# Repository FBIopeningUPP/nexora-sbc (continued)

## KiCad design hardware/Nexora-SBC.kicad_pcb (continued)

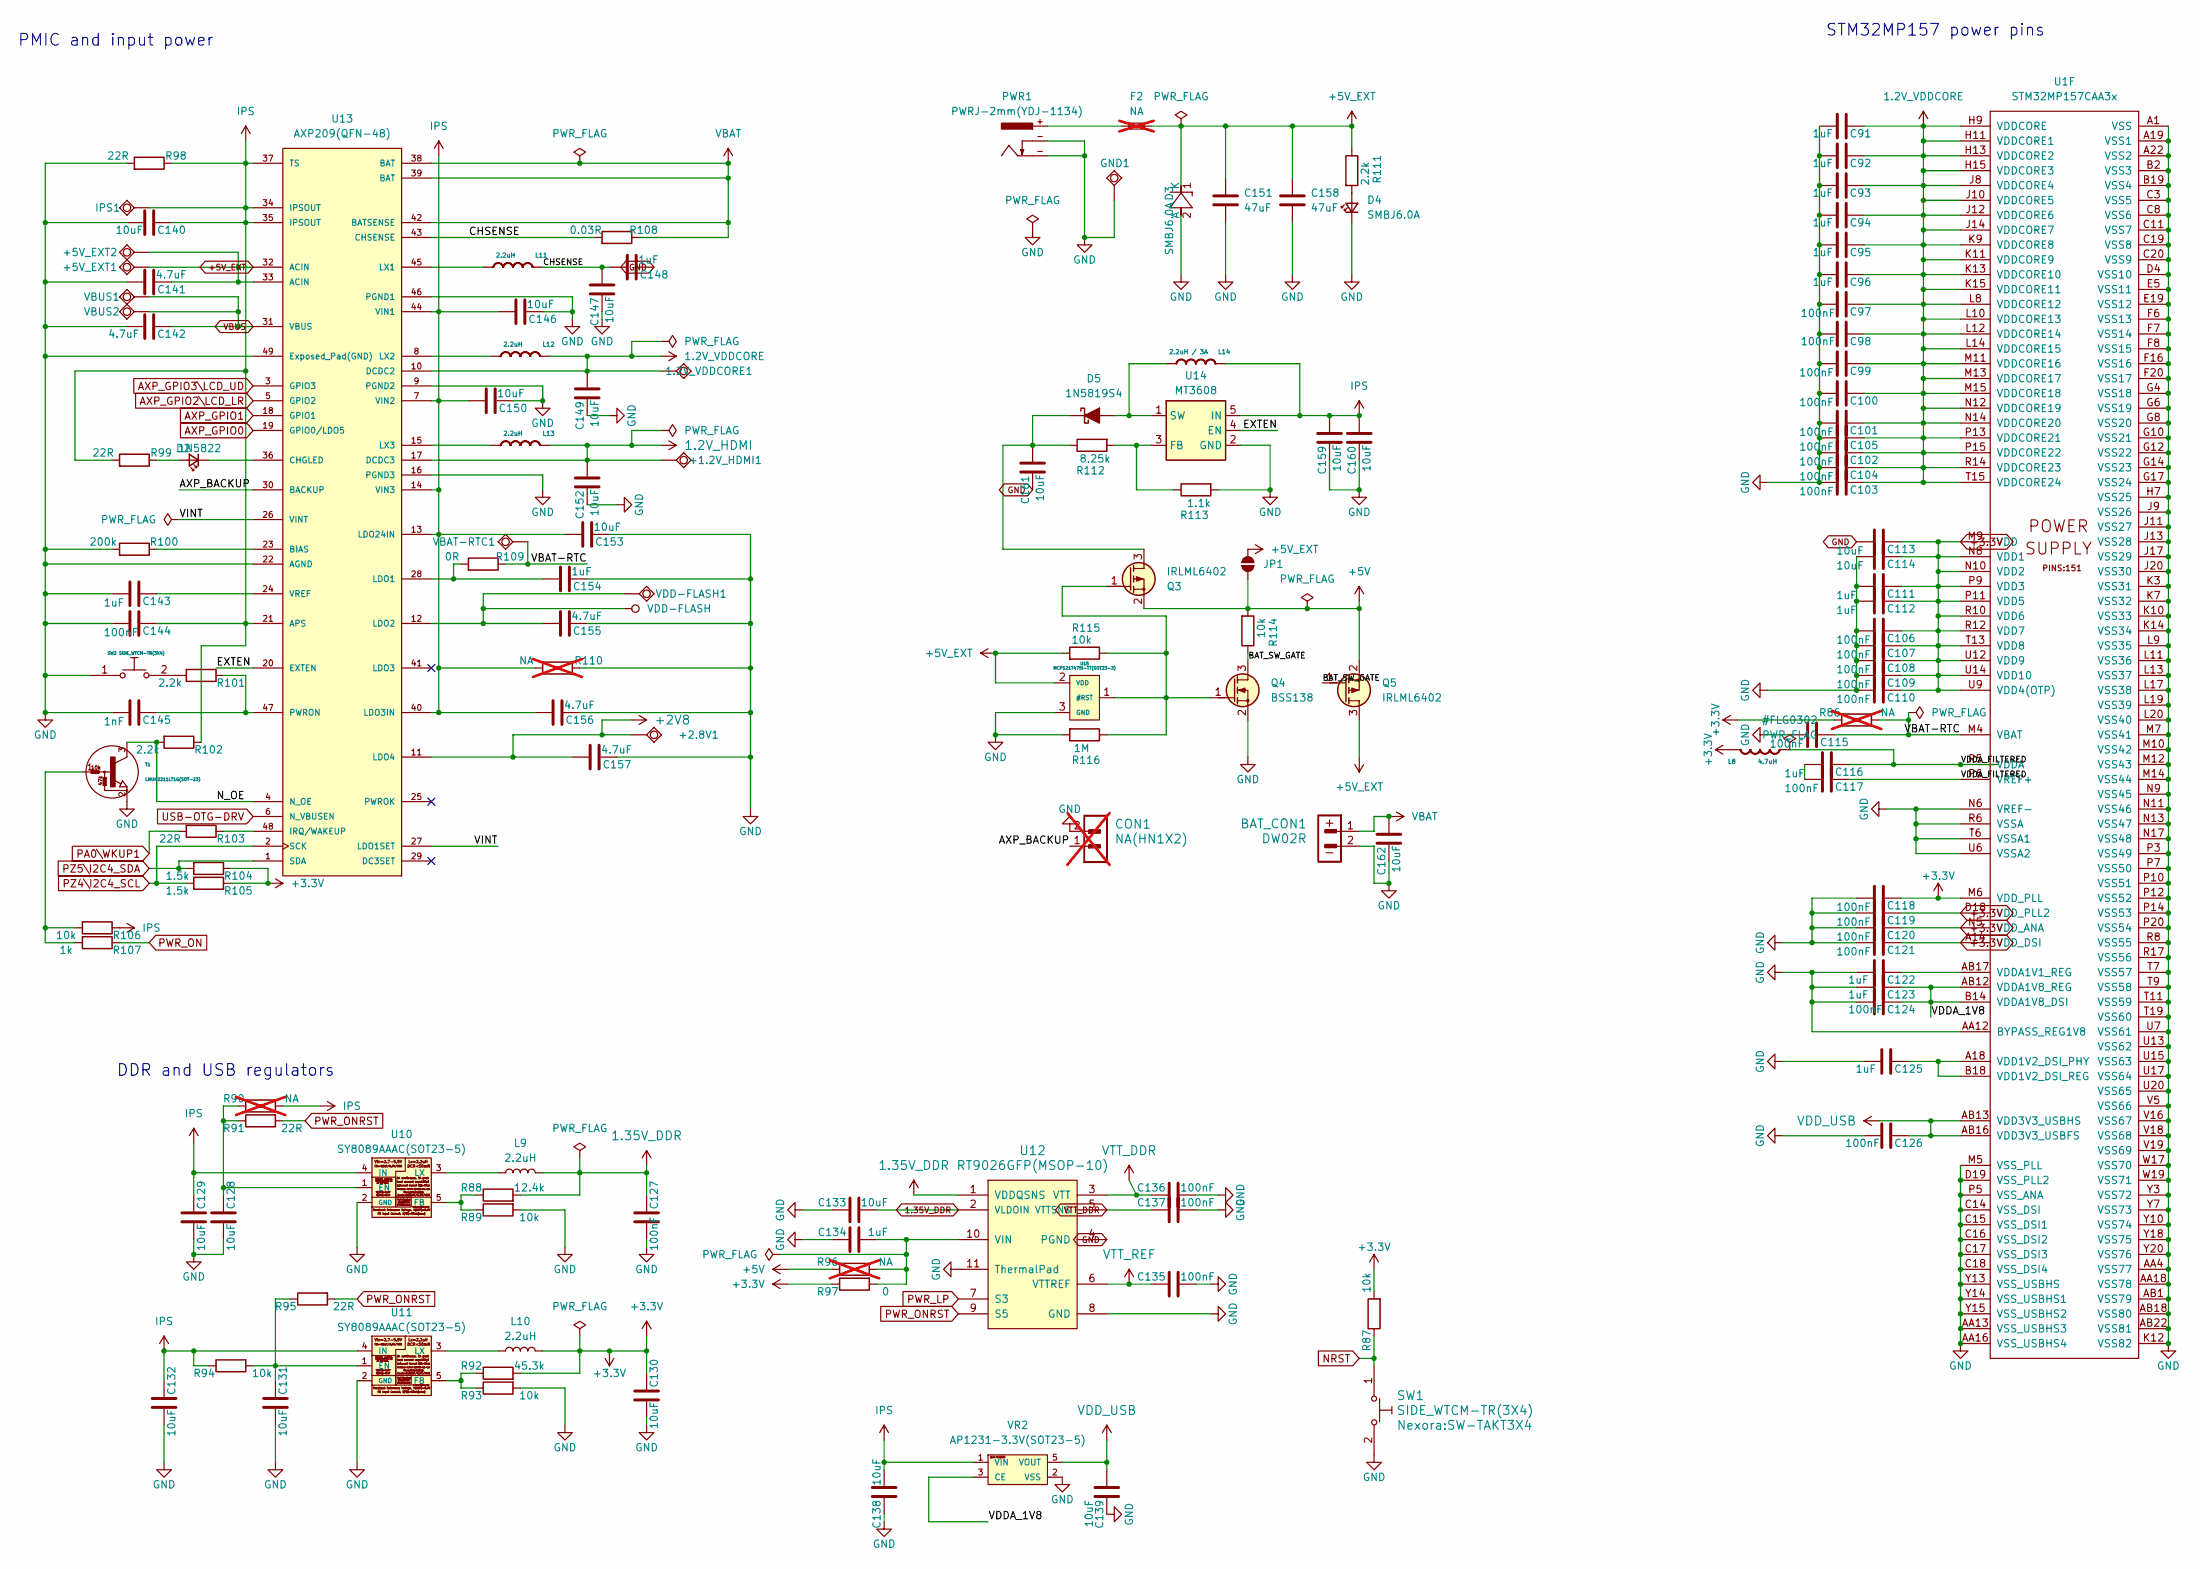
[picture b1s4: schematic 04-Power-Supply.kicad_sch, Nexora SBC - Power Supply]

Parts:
1.2V_VDDCORE1: TESTPAD; TP_SMD
+1.2V_HDMI1, +2.8V1, +5V_EXT1, +5V_EXT2: TESTPAD; TP_SMD
BAT_CON1: DW02R; LIPO_BAT-CON2DW02R
C91, C92, C93, C94, C95, C96, C111, C112, C116, C122, C123, C125, C134, C143, C148, C154: 1uF; C_0402_1005Metric
C97, C98, C99, C100, C101, C102, C103, C104, C105, C106, C107, C108, C109, C110, C115, C117, C118, C119, C120, C121, C124, C126, C127, C135, C136, C137, C144: 100nF; C_0402_1005Metric
C113, C114, C128, C129, C130, C131, C132, C133, C138, C139, C140, C146, C147, C149, C150, C152, C153, C159, C160, C161, C162: 10uF; C_0402_1005Metric
C141, C142, C155, C156, C157: 4.7uF; C_0402_1005Metric
C145: 1nF; C_0402_1005Metric
C151, C158: 47uF; C_0805_2012Metric
CON1: NA(HN1X2); HN1x2; not fitted
D2: 1N5822; D_SMA
D3, D4: SMBJ6.0A; D_SMB
D5: 1N5819S4; D_SOD-123
F2: NA; Fuse_2010_5025Metric; not fitted
GND1: TESTPAD; TP_SMD
IPS1: TESTPAD; TP_SMD
JP1: Jumper_2_NO
L8: 4.7uH; L_0805_2012Metric; Rating A
L9, L10: 2.2uH; L_APV_ANR3015; Part Number MPZ1608S102ATA00; JLCPCB ID C76814
L11, L12, L13: 2.2uH; CD32; Rating A
L14: 2.2uH / 3A; YS75_7X8MM; Rating A
PWR1: PWRJ-2mm(YDJ-1134)
Q3, Q5: IRLML6402; SOT-23
Q4: BSS138; SOT-23
R86, R90, R96, R110: NA; R_0402_1005Metric; not fitted
R87, R89, R93, R94, R106, R114, R115: 10k; R_0402_1005Metric
R88: 12.4k; R_0402_1005Metric
R91, R95, R98, R99, R103: 22R; R_0402_1005Metric
R92: 45.3k; R_0402_1005Metric
R97: 0; R_0402_1005Metric
R100: 200k; R_0402_1005Metric
R101, R102, R111: 2.2k; R_0402_1005Metric
R104, R105: 1.5k; R_0402_1005Metric
R107: 1k; R_0402_1005Metric
R108: 0.03R; R_0402_1005Metric
R109: 0R; R_0402_1005Metric
R112: 8.25k; R_0402_1005Metric
R113: 1.1k; R_0402_1005Metric
R116: 1M; R_0402_1005Metric
SW1, SW2: SIDE_WTCM-TR(3X4); SW-TAKT3X4
T1: LMUN2211LT1G(SOT-23); SOT-23
U1: STM32MP157CAA3x; LFBGA-448(Pitch-0.8mm_Pad-0.4mm_18x18x1.27mm)
U10, U11: SY8089AAAC(SOT23-5); SOT-23-5
U12: RT9026GFP(MSOP-10); MSOP-10-EP_Pitch-0.5mm_3.00x3.00x1.00mm
U13: AXP209(QFN-48); QFN48-6x6mm-OLIMEX_V2
U14: MT3608; SOT-23-6
U15: MCP121T475I-TT(SOT23-3); SOT-23
VBAT-RTC1: TESTPAD; TP_SMD
VBUS1, VBUS2: TESTPAD; TP_SMD
VDD-FLASH1: TESTPAD; TP_SMD
VR2: AP1231-3.3V(SOT23-5); SOT-23-5

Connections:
1.2V_HDMI: +1.2V_HDMI1.1 (Pad_1), C152.2, L13.1 (+), U13.17 (DCDC3); also elsewhere on the board
1.2V_VDDCORE: 1.2V_VDDCORE1.1 (Pad_1), C91.1, C92.1, C93.1, C94.1, C95.1, C96.1, C97.1, C98.1, C99.1, C100.1, C101.1, C102.1, C103.1, C104.1, C105.1, C149.2, L12.1 (+), U1.H9 (VDDCORE), U1.H11 (VDDCORE1), U1.H13 (VDDCORE2), U1.H15 (VDDCORE3), U1.J8 (VDDCORE4), U1.J10 (VDDCORE5), U1.J12 (VDDCORE6), U1.J14 (VDDCORE7), U1.K9 (VDDCORE8), U1.K11 (VDDCORE9), U1.K13 (VDDCORE10), U1.K15 (VDDCORE11), U1.L8 (VDDCORE12), U1.L10 (VDDCORE13), U1.L12 (VDDCORE14), U1.L14 (VDDCORE15), U1.M11 (VDDCORE16), U1.M13 (VDDCORE17), U1.M15 (VDDCORE18), U1.N12 (VDDCORE19), U1.N14 (VDDCORE20), U1.P13 (VDDCORE21), U1.P15 (VDDCORE22), U1.R14 (VDDCORE23), U1.T15 (VDDCORE24), U13.10 (DCDC2)
1.35V_DDR: C127.1, C133.2, L9.2, R88.1, U12.1 (VDDQSNS), U12.2 (VLDOIN); also elsewhere on the board
+2V8: +2.8V1.1 (Pad_1), C157.2, U13.11 (LDO4); also elsewhere on the board
+3.3V: C106.1, C107.1, C108.1, C109.1, C110.1, C111.1, C112.1, C113.1, C114.1, C118.1, C119.1, C120.1, C121.1, C130.1, L8.1 (+), L10.2, R86.2, R87.1, R92.1, R97.2, R104.2, R105.2, U1.A14 (VDD_DSI), U1.D18 (VDD_PLL2), U1.M6 (VDD_PLL), U1.M9 (VDD), U1.N5 (VDD_ANA), U1.N8 (VDD1), U1.N10 (VDD2), U1.P9 (VDD3), U1.P11 (VDD5), U1.R10 (VDD6), U1.R12 (VDD7), U1.T13 (VDD8), U1.U9 (VDD4(OTP)), U1.U12 (VDD9), U1.U14 (VDD10); also elsewhere on the board
+5V: JP1.1 (A), Q3.2 (S), Q5.2 (S), R96.2, R114.1; also elsewhere on the board
+5V_EXT: +5V_EXT1.1 (Pad_1), +5V_EXT2.1 (Pad_1), C141.1, C151.1, C158.1, D3.1 (K), F2.2, JP1.2 (B), Q5.3 (D), R111.2, R115.1, U13.32 (ACIN), U13.33 (ACIN), U15.2 (VDD)
/Power Supply/AXP_BACKUP: CON1.1, U13.30 (BACKUP)
/Power Supply/BAT_SW_GATE: Q4.3 (D), Q5.1 (G), R114.2
/Power Supply/CHSENSE: C147.2, C148.2, L11.1 (+), R108.1, U13.43 (CHSENSE)
/Power Supply/EXTEN: U13.20 (EXTEN), U14.4 (EN)
/Power Supply/N_OE: R102.1, T1.3 (C), U13.4 (N_OE)
/Power Supply/VBAT-RTC: C115.1, R86.1, R109.2, U1.M4 (VBAT), VBAT-RTC1.1 (Pad_1)
/Power Supply/VDDA_1V8: C123.1, C124.1, U1.AB12 (VDDA1V8_REG), U1.B14 (VDDA1V8_DSI), VR2.3 (CE)
/Power Supply/VDDA_FILTERED: C116.1, C117.1, L8.2 (-), U1.P6 (VREF+), U1.R5 (VDDA)
/Power Supply/VINT: U13.26 (VINT), U13.27 (LDO1SET)
AXP_GPIO0: U13.19 (GPIO0/LDO5); also elsewhere on the board
AXP_GPIO1: U13.18 (GPIO1); also elsewhere on the board
AXP_GPIO2\LCD_LR: U13.5 (GPIO2); also elsewhere on the board
AXP_GPIO3\LCD_UD: U13.3 (GPIO3); also elsewhere on the board
GND: BAT_CON1.2, C91.2, C92.2, C93.2, C94.2, C95.2, C96.2, C97.2, C98.2, C99.2, C100.2, C101.2, C102.2, C103.2, C104.2, C105.2, C106.2, C107.2, C108.2, C109.2, C110.2, C111.2, C112.2, C113.2, C114.2, C115.2, C118.2, C119.2, C120.2, C121.2, C122.2, C123.2, C124.2, C125.2, C126.2, C127.2, C128.2, C129.2, C130.2, C131.2, C132.2, C133.1, C134.1, C135.2, C136.2, C137.2, C138.1, C139.1, C140.2, C141.2, C142.2, C143.2, C144.2, C145.2, C146.1, C147.1, C148.1, C149.1, C150.1, C151.2, C152.1, C153.1, C154.1, C155.1, C156.1, C157.1, C158.2, C159.1, C160.1, C161.1, C162.1, CON1.2, D3.2 (A), D4.1 (K), GND1.1 (Pad_1), PWR1.-, Q4.2 (S), R89.1, R93.1, R98.1, R100.1, R110.2, R113.1, R116.1, SW1.2, SW2.1, T1.2 (E), U1.A1 (VSS), U1.A19 (VSS1), U1.A22 (VSS2), U1.AA4 (VSS77), U1.AA12 (BYPASS_REG1V8), U1.AA13 (VSS_USBHS3), U1.AA16 (VSS_USBHS4), U1.AA18 (VSS78), U1.AB1 (VSS79), U1.AB18 (VSS80), U1.AB22 (VSS81), U1.B2 (VSS3), U1.B19 (VSS4), U1.C3 (VSS5), U1.C8 (VSS6), U1.C11 (VSS7), U1.C14 (VSS_DSI), U1.C15 (VSS_DSI1), U1.C16 (VSS_DSI2), U1.C17 (VSS_DSI3), U1.C18 (VSS_DSI4), U1.C19 (VSS8), U1.C20 (VSS9), U1.D4 (VSS10), U1.D19 (VSS_PLL2), U1.E5 (VSS11), U1.E19 (VSS12), U1.F6 (VSS13), U1.F7 (VSS14), U1.F8 (VSS15), U1.F16 (VSS16), U1.F20 (VSS17), U1.G4 (VSS18), U1.G6 (VSS19), U1.G8 (VSS20), U1.G10 (VSS21), U1.G12 (VSS22), U1.G14 (VSS23), U1.G17 (VSS24), U1.H7 (VSS25), U1.J9 (VSS26), U1.J11 (VSS27), U1.J13 (VSS28), U1.J17 (VSS29), U1.J20 (VSS30), U1.K3 (VSS31), U1.K7 (VSS32), U1.K10 (VSS33), U1.K12 (VSS82), U1.K14 (VSS34), U1.L9 (VSS35), U1.L11 (VSS36), U1.L13 (VSS37), U1.L17 (VSS38), U1.L19 (VSS39), U1.L20 (VSS40), U1.M5 (VSS_PLL), U1.M7 (VSS41), U1.M10 (VSS42), U1.M12 (VSS43), U1.M14 (VSS44), U1.N6 (VREF-), U1.N9 (VSS45), U1.N11 (VSS46), U1.N13 (VSS47), U1.N17 (VSS48), U1.P3 (VSS49), U1.P5 (VSS_ANA), U1.P7 (VSS50), U1.P10 (VSS51), U1.P12 (VSS52), U1.P14 (VSS53), U1.P20 (VSS54), U1.R6 (VSSA), U1.R8 (VSS55), U1.R17 (VSS56), U1.T6 (VSSA1), U1.T7 (VSS57), U1.T9 (VSS58), U1.T11 (VSS59), U1.T19 (VSS60), U1.U6 (VSSA2), U1.U7 (VSS61), U1.U13 (VSS62), U1.U15 (VSS63), U1.U17 (VSS64), U1.U20 (VSS65), U1.V5 (VSS66), U1.V16 (VSS67), U1.V18 (VSS68), U1.V19 (VSS69), U1.W17 (VSS70), U1.W19 (VSS71), U1.Y3 (VSS72), U1.Y7 (VSS73), U1.Y10 (VSS74), U1.Y13 (VSS_USBHS), U1.Y14 (VSS_USBHS1), U1.Y15 (VSS_USBHS2), U1.Y18 (VSS75), U1.Y20 (VSS76), U10.2 (GND), U11.2 (GND), U12.4 (PGND), U12.8 (GND), U12.11 (ThermalPad), U13.9 (PGND2), U13.16 (PGND3), U13.22 (AGND), U13.46 (PGND1), U13.49 (Exposed_Pad(GND)), U14.2 (GND), U15.3 (GND), VR2.2 (VSS); also elsewhere on the board
IPS: C129.1, C132.1, C138.2, C140.1, C144.1, C146.2, C150.2, C153.2, C156.2, C159.2, C160.2, IPS1.1 (Pad_1), L14.1 (+), R90.1, R94.2, R98.2, R99.1, R102.2, R106.2, R110.1, U10.4 (IN), U11.4 (IN), U13.7 (VIN2), U13.13 (LDO24IN), U13.14 (VIN3), U13.21 (APS), U13.34 (IPSOUT), U13.35 (IPSOUT), U13.37 (TS), U13.40 (LDO3IN), U13.44 (VIN1), U14.5 (IN), VR2.1 (VIN)
NRST: R87.2, SW1.1; also elsewhere on the board
unnamed: C116.2, C117.2
unnamed: D2.2 (A), R99.2
unnamed: D2.1 (K), U13.36 (CHGLED)
unnamed: D4.2 (A), R111.1
unnamed: D5.2 (A), L14.2 (-), U14.1 (SW)
unnamed: C161.2, D5.1 (K), Q3.3 (D), R112.2
unnamed: F2.1, PWR1.+
unnamed: L11.2 (-), U13.45 (LX1)
unnamed: L12.2 (-), U13.8 (LX2)
unnamed: L13.2 (-), U13.15 (LX3)
unnamed: Q3.1 (G), Q4.1 (G), R115.2, R116.2, U15.1 (#RST)
unnamed: R101.1, SW2.2
unnamed: R106.1, R107.1, T1.1 (B)
unnamed: C125.1, U1.A18 (VDD1V2_DSI_PHY), U1.B18 (VDD1V2_DSI_REG)
unnamed: C122.1, U1.AB17 (VDDA1V1_REG)
unnamed: C128.1, R90.2, R91.2, U10.1 (EN)
unnamed: R88.2, R89.2, U10.5 (FB)
unnamed: L9.1, U10.3 (LX)
unnamed: C131.1, R94.1, R95.2, U11.1 (EN)
unnamed: R92.2, R93.2, U11.5 (FB)
unnamed: L10.1, U11.3 (LX)
unnamed: C134.2, R96.1, R97.1, U12.10 (VIN)
unnamed: R100.2, U13.23 (BIAS)
unnamed: R103.2, U13.48 (IRQ/WAKEUP)
unnamed: C154.2, R109.1, U13.28 (LDO1)
unnamed: C145.1, R101.2, U13.47 (PWRON)
unnamed: C143.1, U13.24 (VREF)
unnamed: R112.1, R113.2, U14.3 (FB)
PA0\WKUP1: R103.1; also elsewhere on the board
PWR_LP: U12.7 (S3); also elsewhere on the board
PWR_ON: R107.2; also elsewhere on the board
PWR_ONRST: R91.1, R95.1, U12.9 (S5); also elsewhere on the board
PZ4\I2C4_SCL: R105.1, U13.2 (SCK); also elsewhere on the board
PZ5\I2C4_SDA: R104.1, U13.1 (SDA); also elsewhere on the board
USB-OTG-DRV: U13.6 (N_VBUSEN); also elsewhere on the board
VBAT: BAT_CON1.1, C162.2, R108.2, U13.38 (BAT), U13.39 (BAT), U13.42 (BATSENSE)
VBUS: C142.1, U13.31 (VBUS), VBUS1.1 (Pad_1), VBUS2.1 (Pad_1); also elsewhere on the board
VDD-FLASH: C155.2, U13.12 (LDO2), VDD-FLASH1.1 (Pad_1); also elsewhere on the board
VDD_USB: C126.1, C139.2, U1.AB13 (VDD3V3_USBHS), U1.AB16 (VDD3V3_USBFS), VR2.5 (VOUT)
VTT_DDR: C136.1, C137.1, U12.3 (VTT), U12.5 (VTTSNS); also elsewhere on the board
VTT_REF: C135.1, U12.6 (VTTREF); also elsewhere on the board

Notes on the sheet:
PMIC and input power
DDR and USB regulators
STM32MP157 power pins

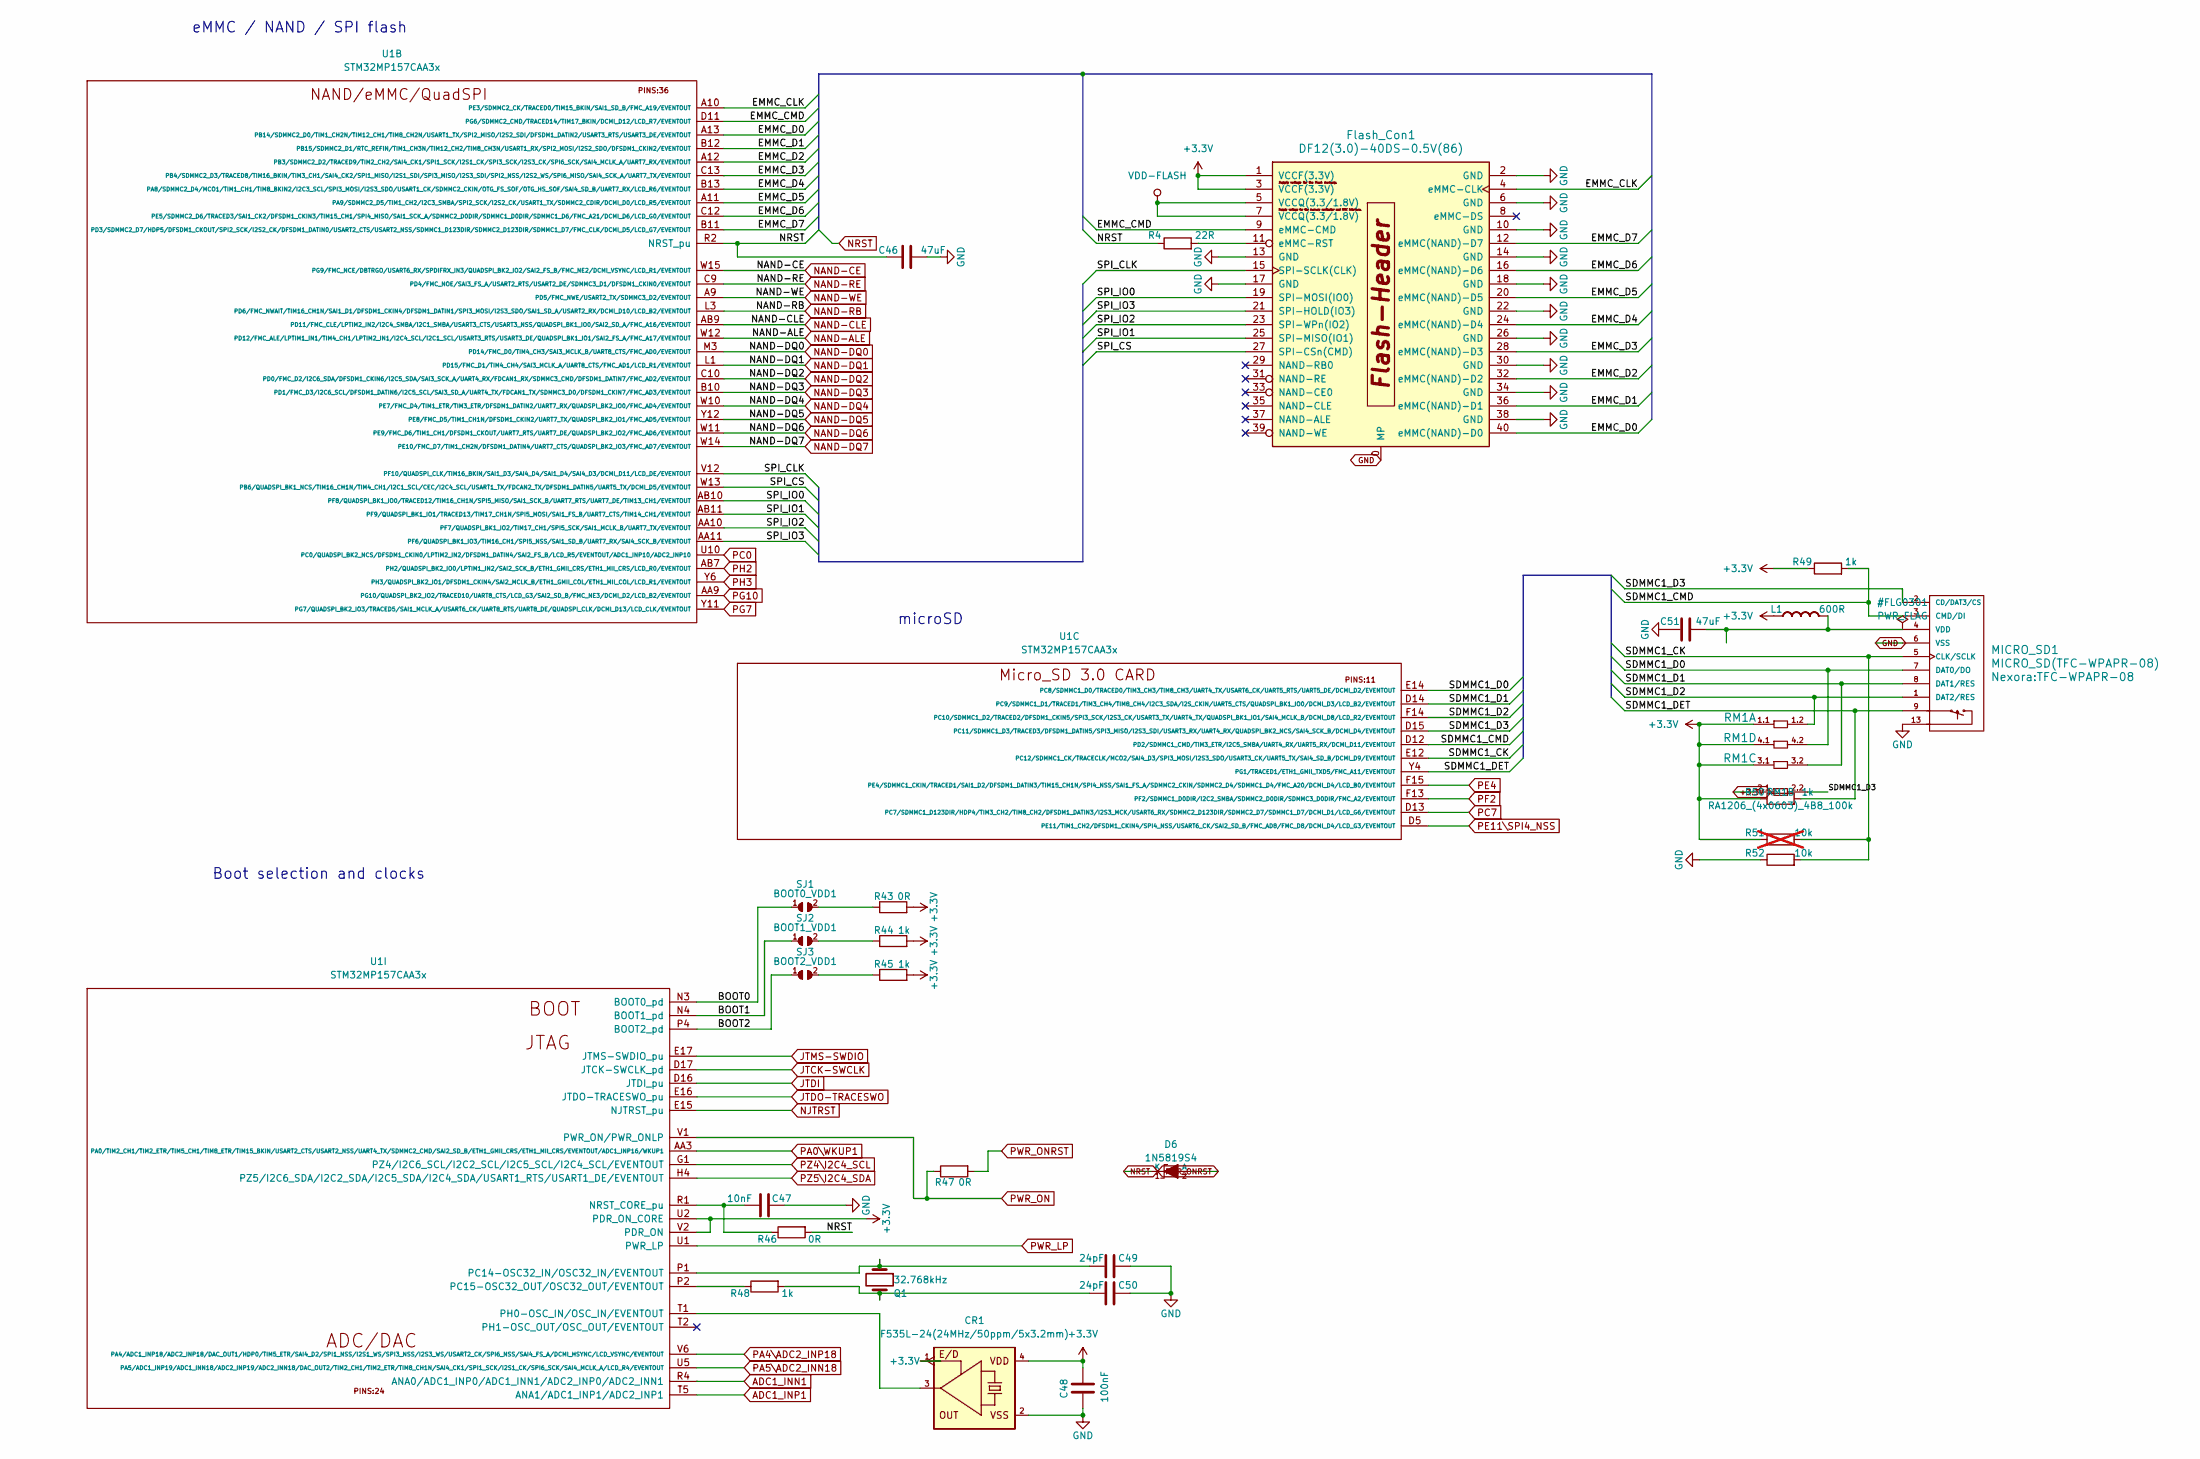
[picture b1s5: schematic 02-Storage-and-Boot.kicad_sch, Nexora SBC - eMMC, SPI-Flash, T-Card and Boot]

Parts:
C46: 47uF; C_0805_2012Metric
C47: 10nF; C_0402_1005Metric
C48: 100nF; C_0402_1005Metric
C49, C50: 24pF; C_0402_1005Metric
C51: 47uF; C_0402_1005Metric
CR1: F535L-24(24MHz/50ppm/5x3.2mm); 5032-4P_HCX-3S
D6: 1N5819S4; D_SOD-123
Flash_Con1: DF12(3.0)-40DS-0.5V(86); Flash_Con[DF12(3.0)-40DS-0.5V(86)]
L1: 600R; L_0805_2012Metric; Rating A
MICRO_SD1: MICRO_SD(TFC-WPAPR-08); TFC-WPAPR-08
Q1: 32.768kHz; CM7V-T1A(Crystal_Package-1206_3.20x1.50x0.65mm)
R4: 22R; R_0402_1005Metric
R43, R46, R47: 0R; R_0402_1005Metric
R44, R45, R48, R49, R50: 1k; R_0402_1005Metric
R51: 10k; R_0402_1005Metric; not fitted
R52: 10k; R_0402_1005Metric
RM1: RA1206_(4x0603)_4B8_100k; RA1206_(4X0603)_4B8_xx
SJ1: BOOT0_VDD1; SJ_1_SMALLER
SJ2: BOOT1_VDD1; SJ_1_SMALLER
SJ3: BOOT2_VDD1; SJ_1_SMALLER
U1: STM32MP157CAA3x; LFBGA-448(Pitch-0.8mm_Pad-0.4mm_18x18x1.27mm)

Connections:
+3.3V: C48.1, CR1.1 (E/D), CR1.4 (VDD), Flash_Con1.1 (VCCF(3.3V)), Flash_Con1.3 (VCCF(3.3V)), L1.1 (+), R43.1, R44.1, R45.1, R49.2, R50.2, R51.2, RM1.1.1, RM1.2.1, RM1.3.1, RM1.4.1, U1.U2 (PDR_ON_CORE), U1.V2 (PDR_ON); also elsewhere on the board
/eMMC, SPI-Flash, T-Card and Boot/BOOT0: SJ1.1, U1.N3 (BOOT0_pd)
/eMMC, SPI-Flash, T-Card and Boot/BOOT1: SJ2.1, U1.N4 (BOOT1_pd)
/eMMC, SPI-Flash, T-Card and Boot/BOOT2: SJ3.1, U1.P4 (BOOT2_pd)
/eMMC, SPI-Flash, T-Card and Boot/EMMC_CLK: Flash_Con1.4 (eMMC-CLK), U1.A10 (PE3/SDMMC2_CK/TRACED0/TIM15_BKIN/SAI1_S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)
/eMMC, SPI-Flash, T-Card and Boot/EMMC_CMD: Flash_Con1.9 (eMMC-CMD), U1.D11 (PG6/SDMMC2_CMD/TRACED14/TIM17_BKIN/DCMI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)
/eMMC, SPI-Flash, T-Card and Boot/EMMC_D0: Flash_Con1.40 (eMMC(NAND)-D0), U1.A13 (PB14/SDMMC2_D0/TIM1_CH2N/TIM12_CH1/TIM8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)
/eMMC, SPI-Flash, T-Card and Boot/EMMC_D1: Flash_Con1.36 (eMMC(NAND)-D1), U1.B12 (PB15/SDMMC2_D1/RTC_REFIN/TIM1_CH3N/TIM1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)
/eMMC, SPI-Flash, T-Card and Boot/EMMC_D2: Flash_Con1.32 (eMMC(NAND)-D2), U1.A12 (PB3/SDMMC2_D2/TRACED9/TIM2_CH2/SAI4_CK1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)
/eMMC, SPI-Flash, T-Card and Boot/EMMC_D3: Flash_Con1.28 (eMMC(NAND)-D3), U1.C13 (PB4/SDMMC2_D3/TRACED8/TIM16_BKIN/TIM3_C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)
/eMMC, SPI-Flash, T-Card and Boot/EMMC_D4: Flash_Con1.24 (eMMC(NAND)-D4), U1.B13 (PA8/SDMMC2_D4/MCO1/TIM1_CH1/TIM8_BKIN2/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)
/eMMC, SPI-Flash, T-Card and Boot/EMMC_D5: Flash_Con1.20 (eMMC(NAND)-D5), U1.A11 (PA9/SDMMC2_D5/TIM1_CH2/I2C3_SMBA/SPI2_S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)
/eMMC, SPI-Flash, T-Card and Boot/EMMC_D6: Flash_Con1.16 (eMMC(NAND)-D6), U1.C12 (PE5/SDMMC2_D6/TRACED3/SAI1_CK2/DFSDM1_C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)
/eMMC, SPI-Flash, T-Card and Boot/EMMC_D7: Flash_Con1.12 (eMMC(NAND)-D7), U1.B11 (PD3/SDMMC2_D7/HDP5/DFSDM1_CKOUT/SPI2_SC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)
/eMMC, SPI-Flash, T-Card and Boot/SDMMC1_CK: MICRO_SD1.5 (CLK/SCLK), R51.1, R52.1, U1.E12 (PC12/SDMMC1_CK/TRACECLK/MCO2/SAI4_D3/SP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)
/eMMC, SPI-Flash, T-Card and Boot/SDMMC1_CMD: MICRO_SD1.3 (CMD/DI), R49.1, U1.D12 (PD2/SDMMC1_CMD/TIM3_ETR/I2C5_SMBA/UART4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)
/eMMC, SPI-Flash, T-Card and Boot/SDMMC1_D0: MICRO_SD1.7 (DAT0/DO), RM1.4.2, U1.E14 (PC8/SDMMC1_D0/TRACED0/TIM3_CH3/TIM8_CH3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)
/eMMC, SPI-Flash, T-Card and Boot/SDMMC1_D1: MICRO_SD1.8 (DAT1/RES), RM1.3.2, U1.D14 (PC9/SDMMC1_D1/TRACED1/TIM3_CH4/TIM8_CH4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)
/eMMC, SPI-Flash, T-Card and Boot/SDMMC1_D2: MICRO_SD1.1 (DAT2/RES), RM1.1.2, U1.F14 (PC10/SDMMC1_D2/TRACED2/DFSDM1_CKIN5/SPI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)
/eMMC, SPI-Flash, T-Card and Boot/SDMMC1_D3: MICRO_SD1.2 (CD/DAT3/CS), RM1.2.2, U1.D15 (PC11/SDMMC1_D3/TRACED3/DFSDM1_DATIN5/SP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)
/eMMC, SPI-Flash, T-Card and Boot/SDMMC1_DET: MICRO_SD1.9, R50.1, U1.Y4 (PG1/TRACED1/ETH1_GMII_TXD5/FMC_A11/EVEN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)
/eMMC, SPI-Flash, T-Card and Boot/SPI_CLK: Flash_Con1.15 (SPI-SCLK(CLK)), U1.V12 (PF10/QUADSPI_CLK/TIM16_BKIN/SAI1_D3/SAI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)
/eMMC, SPI-Flash, T-Card and Boot/SPI_CS: Flash_Con1.27 (SPI-CSn(CMD)), U1.W13 (PB6/QUADSPI_BK1_NCS/TIM16_CH1N/TIM4_CH1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)
/eMMC, SPI-Flash, T-Card and Boot/SPI_IO0: Flash_Con1.19 (SPI-MOSI(IO0)), U1.AB10 (PF8/QUADSPI_BK1_IO0/TRACED12/TIM16_CH1N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)
/eMMC, SPI-Flash, T-Card and Boot/SPI_IO1: Flash_Con1.25 (SPI-MISO(IO1)), U1.AB11 (PF9/QUADSPI_BK1_IO1/TRACED13/TIM17_CH1N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)
/eMMC, SPI-Flash, T-Card and Boot/SPI_IO2: Flash_Con1.23 (SPI-WPn(IO2)), U1.AA10 (PF7/QUADSPI_BK1_IO2/TIM17_CH1/SPI5_SCK/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)
/eMMC, SPI-Flash, T-Card and Boot/SPI_IO3: Flash_Con1.21 (SPI-HOLD(IO3)), U1.AA11 (PF6/QUADSPI_BK1_IO3/TIM16_CH1/SPI5_NSS/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)
ADC1_INN1: U1.R4 (ANA0/ADC1_INP0/ADC1_INN1/ADC2_INP0/ADC2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); also elsewhere on the board
ADC1_INP1: U1.T5 (ANA1/ADC1_INP1/ADC2_INP1); also elsewhere on the board
GND: C46.2, C47.1, C48.2, C49.2, C50.2, C51.1, CR1.2 (VSS), Flash_Con1.0 (MP), Flash_Con1.2 (GND), Flash_Con1.6 (GND), Flash_Con1.10 (GND), Flash_Con1.13 (GND), Flash_Con1.14 (GND), Flash_Con1.17 (GND), Flash_Con1.18 (GND), Flash_Con1.22 (GND), Flash_Con1.26 (GND), Flash_Con1.30 (GND), Flash_Con1.34 (GND), Flash_Con1.38 (GND), MICRO_SD1.6 (VSS), MICRO_SD1.10, MICRO_SD1.11, MICRO_SD1.12, MICRO_SD1.13, R52.2; also elsewhere on the board
JTCK-SWCLK: U1.D17 (JTCK-SWCLK_pd); also elsewhere on the board
JTDI: U1.D16 (JTDI_pu); also elsewhere on the board
JTDO-TRACESWO: U1.E16 (JTDO-TRACESWO_pu); also elsewhere on the board
JTMS-SWDIO: U1.E17 (JTMS-SWDIO_pu); also elsewhere on the board
NAND-ALE: U1.W12 (PD12/FMC_ALE/LPTIM1_IN1/TIM4_CH1/LPTIM2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); also elsewhere on the board
NAND-CE: U1.W15 (PG9/FMC_NCE/DBTRGO/USART6_RX/SPDIFRX_IN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); also elsewhere on the board
NAND-CLE: U1.AB9 (PD11/FMC_CLE/LPTIM2_IN2/I2C4_SMBA/I2C1_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); also elsewhere on the board
NAND-DQ0: U1.M3 (PD14/FMC_D0/TIM4_CH3/SAI3_MCLK_B/UART8_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); also elsewhere on the board
NAND-DQ1: U1.L1 (PD15/FMC_D1/TIM4_CH4/SAI3_MCLK_A/UART8_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); also elsewhere on the board
NAND-DQ2: U1.C10 (PD0/FMC_D2/I2C6_SDA/DFSDM1_CKIN6/I2C5_S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); also elsewhere on the board
NAND-DQ3: U1.B10 (PD1/FMC_D3/I2C6_SCL/DFSDM1_DATIN6/I2C5_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); also elsewhere on the board
NAND-DQ4: U1.W10 (PE7/FMC_D4/TIM1_ETR/TIM3_ETR/DFSDM1_DAT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); also elsewhere on the board
NAND-DQ5: U1.Y12 (PE8/FMC_D5/TIM1_CH1N/DFSDM1_CKIN2/UART7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); also elsewhere on the board
NAND-DQ6: U1.W11 (PE9/FMC_D6/TIM1_CH1/DFSDM1_CKOUT/UART7_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); also elsewhere on the board
NAND-DQ7: U1.W14 (PE10/FMC_D7/TIM1_CH2N/DFSDM1_DATIN4/UAR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); also elsewhere on the board
NAND-RB: U1.L3 (PD6/FMC_NWAIT/TIM16_CH1N/SAI1_D1/DFSDM1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); also elsewhere on the board
NAND-RE: U1.C9 (PD4/FMC_NOE/SAI3_FS_A/USART2_RTS/USART2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); also elsewhere on the board
NAND-WE: U1.A9 (PD5/FMC_NWE/USART2_TX/SDMMC3_D2/EVENTOUT); also elsewhere on the board
NJTRST: U1.E15 (NJTRST_pu); also elsewhere on the board
NRST: C46.1, D6.1 (K), R4.2, R46.1, U1.R2 (NRST_pu); also elsewhere on the board
unnamed: C50.1, Q1.2, R48.1
unnamed: CR1.3 (OUT), U1.T1 (PH0-OSC_IN/OSC_IN/EVENTOUT)
unnamed: Flash_Con1.11 (eMMC-RST), R4.1
unnamed: C51.2, L1.2 (-), MICRO_SD1.4 (VDD)
unnamed: R43.2, SJ1.2
unnamed: R44.2, SJ2.2
unnamed: R45.2, SJ3.2
unnamed: C47.2, R46.2, U1.R1 (NRST_CORE_pu)
unnamed: C49.1, Q1.1, U1.P1 (PC14-OSC32_IN/OSC32_IN/EVENTOUT)
unnamed: R48.2, U1.P2 (PC15-OSC32_OUT/OSC32_OUT/EVENTOUT)
PA0\WKUP1: U1.AA3 (PA0/TIM2_CH1/TIM2_ETR/TIM5_CH1/TIM8_ETR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); also elsewhere on the board
PA4\ADC2_INP18: U1.V6 (PA4/ADC1_INP18/ADC2_INP18/DAC_OUT1/HDP0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); also elsewhere on the board
PA5\ADC2_INN18: U1.U5 (PA5/ADC1_INP19/ADC1_INN18/ADC2_INP19/AD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); also elsewhere on the board
PC0: U1.U10 (PC0/QUADSPI_BK2_NCS/DFSDM1_CKIN0/LPTIM2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); also elsewhere on the board
PC7: U1.D13 (PC7/SDMMC1_D123DIR/HDP4/TIM3_CH2/TIM8_C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); also elsewhere on the board
PE4: U1.F15 (PE4/SDMMC1_CKIN/TRACED1/SAI1_D2/DFSDM1_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); also elsewhere on the board
PE11\SPI4_NSS: U1.D5 (PE11/TIM1_CH2/DFSDM1_CKIN4/SPI4_NSS/USA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); also elsewhere on the board
PF2: U1.F13 (PF2/SDMMC1_D0DIR/I2C2_SMBA/SDMMC2_D0DIR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); also elsewhere on the board
PG7: U1.Y11 (PG7/QUADSPI_BK2_IO3/TRACED5/SAI1_MCLK_A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); also elsewhere on the board
PG10: U1.AA9 (PG10/QUADSPI_BK2_IO2/TRACED10/UART8_CTS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); also elsewhere on the board
PH2: U1.AB7 (PH2/QUADSPI_BK2_IO0/LPTIM1_IN2/SAI2_SCK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); also elsewhere on the board
PH3: U1.Y6 (PH3/QUADSPI_BK2_IO1/DFSDM1_CKIN4/SAI2_M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); also elsewhere on the board
PWR_LP: U1.U1 (PWR_LP); also elsewhere on the board
PWR_ON: R47.2, U1.V1 (PWR_ON/PWR_ONLP); also elsewhere on the board
PWR_ONRST: D6.2 (A), R47.1; also elsewhere on the board
PZ4\I2C4_SCL: U1.G1 (PZ4/I2C6_SCL/I2C2_SCL/I2C5_SCL/I2C4_SCL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); also elsewhere on the board
PZ5\I2C4_SDA: U1.H4 (PZ5/I2C6_SDA/I2C2_SDA/I2C5_SDA/I2C4_SDA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); also elsewhere on the board
VDD-FLASH: Flash_Con1.5 (VCCQ(3.3/1.8V)), Flash_Con1.7 (VCCQ(3.3/1.8V)); also elsewhere on the board

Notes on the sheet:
eMMC / NAND / SPI flash
microSD
Boot selection and clocks

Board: 6 copper layers, 407 parts (0 on the bottom side), 422 nets, no tracks yet.
